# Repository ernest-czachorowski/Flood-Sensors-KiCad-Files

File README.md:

# Flood-Sensors-KiCad-Files

This repository contains KiCad files for my master's thesis IoT infrastructure, which includes water leak detection sensors. It does not include any source code as it is the intellectual property of the Nicolaus Copernicus University in Torun and cannot be published here. The infrastructure is divided into a web service made with Node.js and EJS, a PCB master board that communicates with the web service using TCP or UDP protocols, and a set of leak detection sensors that communicate with the master using the Modbus protocol and notify it when a leak is detected. The Master board sends a notification message to the web service about the leak.

### Folder Structure:

- Master - KiCad project of the Master PCB
- Slave - KiCad project of the Slave PCB
- Datasheet - datasheets of used chips/components
- KiCad_symbols - KiCad library files made by me
- Pictures - some pictures

### Master Board:

The Master board is responsible for managing communication between the web service and the Slave boards. It features an ATmega128 microcontroller, which has more RAM memory than the ATmega32 mentioned in the documentation. Communication with the web service is handled by the ENC28J60 chip, and to communicate with slaves, the MAX485 chip is used.

### Slave Board:

The Slave board detects water leaks and communicates with the Master board using the MAX485 chip. It features an LM393 chip for detecting the leak and is controlled by an ATmega32 microcontroller.

### Web Service:

The web service is built using Node.js and EJS and is responsible for receiving notification messages from the Master board about water leaks. It allows users to view the status of the system.

### License:

This project is licensed under the MIT License - see the LICENSE file for details.

### Working devices:

### Master board:

### Slave board:

### Prototype board:

### Prototype board:

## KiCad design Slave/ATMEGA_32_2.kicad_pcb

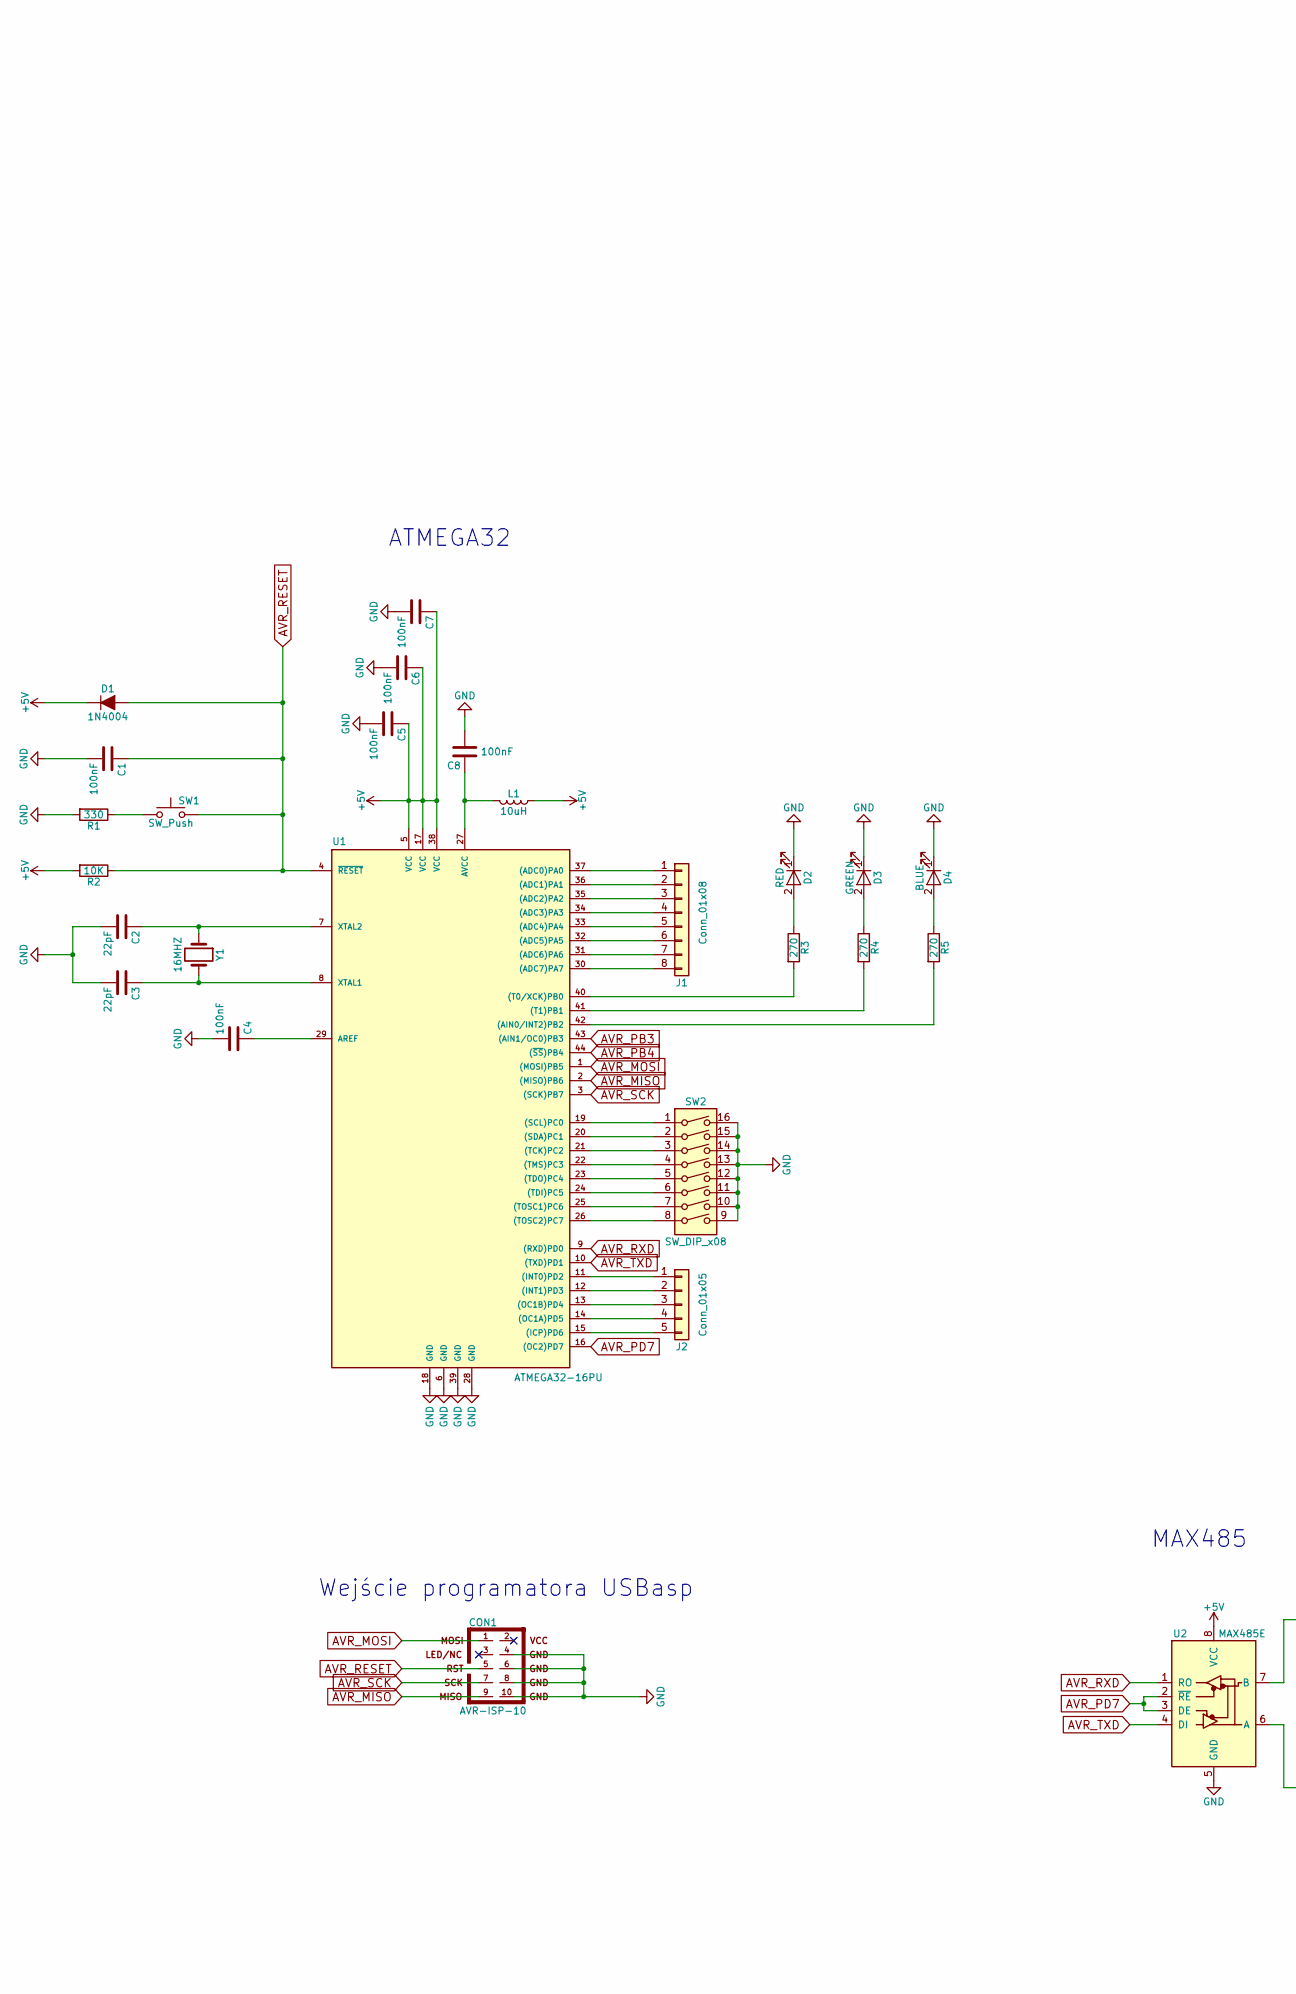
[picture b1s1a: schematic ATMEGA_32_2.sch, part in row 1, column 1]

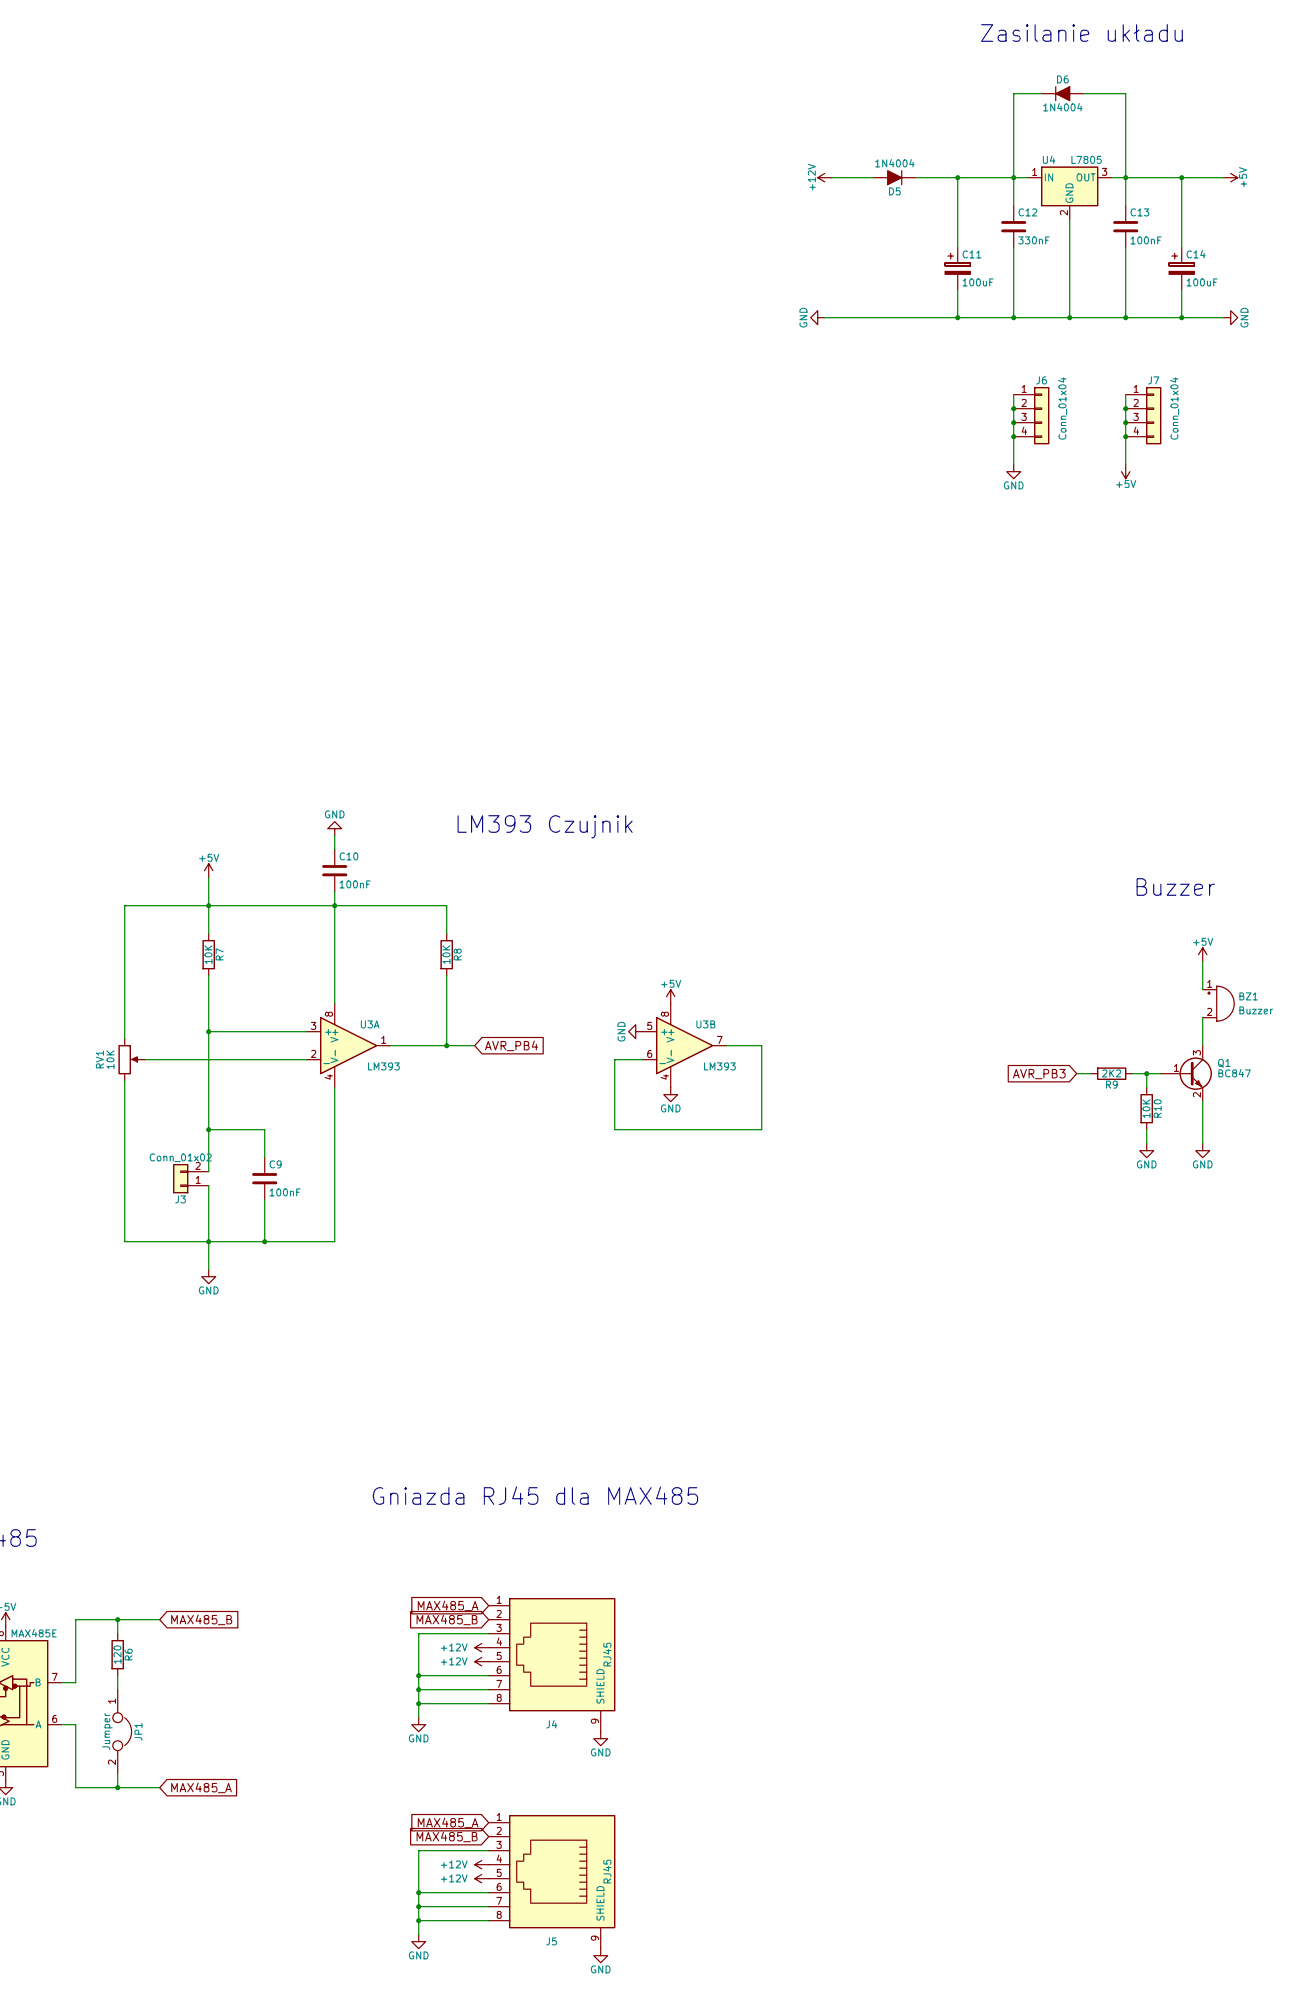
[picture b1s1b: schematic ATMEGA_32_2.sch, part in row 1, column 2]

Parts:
BZ1: Buzzer; Buzzer_12x9.5RM7.6
C1, C4, C5, C6, C7, C8, C9, C10, C13: 100nF; C_1206_HandSoldering
C2, C3: 22pF; C_1206_HandSoldering
C11, C14: 100uF; CP_Elec_6.3x5.3
C12: 330nF; C_1206_HandSoldering
CON1: AVR-ISP-10; Pin_Header_Straight_2x05_Pitch2.54mm
D1, D5, D6: 1N4004; D_DO-35_SOD27_P7.62mm_Horizontal
D2: RED; LED_1206_HandSoldering
D3: GREEN; LED_1206_HandSoldering
D4: BLUE; LED_1206_HandSoldering
J1: Conn_01x08; Pin_Header_Straight_1x08_Pitch2.54mm
J2: Conn_01x05; Pin_Header_Straight_1x05_Pitch2.54mm
J3: Conn_01x02; Pin_Header_Straight_1x02_Pitch2.54mm
J4, J5: RJ45; RJ45_8
J6, J7: Conn_01x04; Pin_Header_Straight_1x04_Pitch2.54mm
JP1: Jumper; Pin_Header_Straight_1x02_Pitch2.54mm
L1: 10uH; L_1206_HandSoldering
Q1: BC847; SOT-23
R1: 330; R_1206_HandSoldering
R2, R7, R8, R10: 10K; R_1206_HandSoldering
R3, R4, R5: 270; R_1206_HandSoldering
R6: 120; R_1206_HandSoldering
R9: 2K2; R_1206_HandSoldering
RV1: 10K; Potentiometer_Trimmer_ACP_CA6v_Horizontal
SW1: SW_Push; SW_PUSH_6mm_h13mm
SW2: SW_DIP_x08; SW_DIP_x8_W7.62mm_Slide
U1: ATMEGA32-16PU; TQFP-44_10x10mm_Pitch0.8mm
U2: MAX485E; SOIC-8_3.9x4.9mm_Pitch1.27mm
U3: LM393; SOIC-8_3.9x4.9mm_Pitch1.27mm
U4: L7805; TO-220-3_Vertical
Y1: 16MHZ; Crystal_HC49-U_Vertical

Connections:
+5V: BZ1.1 (-), C5.1, C6.1, C7.1, C10.2, C13.1, C14.1, D1.1 (K), D6.2 (A), J7.1, J7.2, J7.3, J7.4, L1.1, R2.2, R7.1, R8.1, RV1.1, U1.5 (VCC), U1.17 (VCC), U1.38 (VCC), U2.8 (VCC), U3.8 (V+), U4.3 (OUT)
+12V: D5.2 (A), J4.4, J4.5, J5.4, J5.5
AVR_MISO: CON1.9, U1.2 ((MISO)PB6)
AVR_MOSI: CON1.1, U1.1 ((MOSI)PB5)
AVR_PB3: R9.2, U1.43 ((AIN1/OC0)PB3)
AVR_PB4: R8.2, U1.44 ((~SS~)PB4), U3.1
AVR_PD7: U1.16 ((OC2)PD7), U2.2 (~RE), U2.3 (DE)
AVR_RESET: C1.1, CON1.5, D1.2 (A), R2.1, SW1.2, U1.4 (~RESET)
AVR_RXD: U1.9 ((RXD)PD0), U2.1 (RO)
AVR_SCK: CON1.7, U1.3 ((SCK)PB7)
AVR_TXD: U1.10 ((TXD)PD1), U2.4 (DI)
GND: C1.2, C2.2, C3.2, C4.2, C5.2, C6.2, C7.2, C8.2, C9.2, C10.1, C11.2, C12.2, C13.2, C14.2, CON1.4, CON1.6, CON1.8, CON1.10, D2.1 (K), D3.1 (K), D4.1 (K), J3.1, J4.3, J4.6, J4.7, J4.8, J4.9 (SHIELD), J5.3, J5.6, J5.7, J5.8, J5.9 (SHIELD), J6.1, J6.2, J6.3, J6.4, Q1.2 (E), R1.2, R10.2, RV1.3, SW2.9, SW2.10, SW2.11, SW2.12, SW2.13, SW2.14, SW2.15, SW2.16, U1.6 (GND), U1.18 (GND), U1.28 (GND), U1.39 (GND), U2.5 (GND), U3.4 (V-), U3.5 (+), U4.2 (GND)
MAX485_A: J4.1, J5.1, JP1.2, U2.6 (A)
MAX485_B: J4.2, J5.2, R6.1, U2.7 (B)
unnamed: BZ1.2 (+), Q1.3 (C)
unnamed: C2.1, U1.7 (XTAL2), Y1.1
unnamed: C3.1, U1.8 (XTAL1), Y1.2
unnamed: C4.1, U1.29 (AREF)
unnamed: C8.1, L1.2, U1.27 (AVCC)
unnamed: C9.1, J3.2, R7.2, U3.3 (+)
unnamed: C11.1, C12.1, D5.1 (K), D6.1 (K), U4.1 (IN)
unnamed: D2.2 (A), R3.1
unnamed: D3.2 (A), R4.1
unnamed: D4.2 (A), R5.1
unnamed: J1.1, U1.37 ((ADC0)PA0)
unnamed: J1.2, U1.36 ((ADC1)PA1)
unnamed: J1.3, U1.35 ((ADC2)PA2)
unnamed: J1.4, U1.34 ((ADC3)PA3)
unnamed: J1.5, U1.33 ((ADC4)PA4)
unnamed: J1.6, U1.32 ((ADC5)PA5)
unnamed: J1.7, U1.31 ((ADC6)PA6)
unnamed: J1.8, U1.30 ((ADC7)PA7)
unnamed: J2.1, U1.11 ((INT0)PD2)
unnamed: J2.2, U1.12 ((INT1)PD3)
unnamed: J2.3, U1.13 ((OC1B)PD4)
unnamed: J2.4, U1.14 ((OC1A)PD5)
unnamed: J2.5, U1.15 ((ICP)PD6)
unnamed: JP1.1, R6.2
unnamed: Q1.1 (B), R9.1, R10.1
unnamed: R1.1, SW1.1
unnamed: R3.2, U1.40 ((T0/XCK)PB0)
unnamed: R4.2, U1.41 ((T1)PB1)
unnamed: R5.2, U1.42 ((AIN0/INT2)PB2)
unnamed: RV1.2, U3.2 (_)
unnamed: SW2.1, U1.19 ((SCL)PC0)
unnamed: SW2.2, U1.20 ((SDA)PC1)
unnamed: SW2.3, U1.21 ((TCK)PC2)
unnamed: SW2.4, U1.22 ((TMS)PC3)
unnamed: SW2.5, U1.23 ((TDO)PC4)
unnamed: SW2.6, U1.24 ((TDI)PC5)
unnamed: SW2.7, U1.25 ((TOSC1)PC6)
unnamed: SW2.8, U1.26 ((TOSC2)PC7)
unnamed: U3.6 (_), U3.7

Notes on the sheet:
Wejście programatora USBasp
ATMEGA32
Zasilanie układu
MAX485
Gniazda RJ45 dla MAX485
LM393 Czujnik
Buzzer

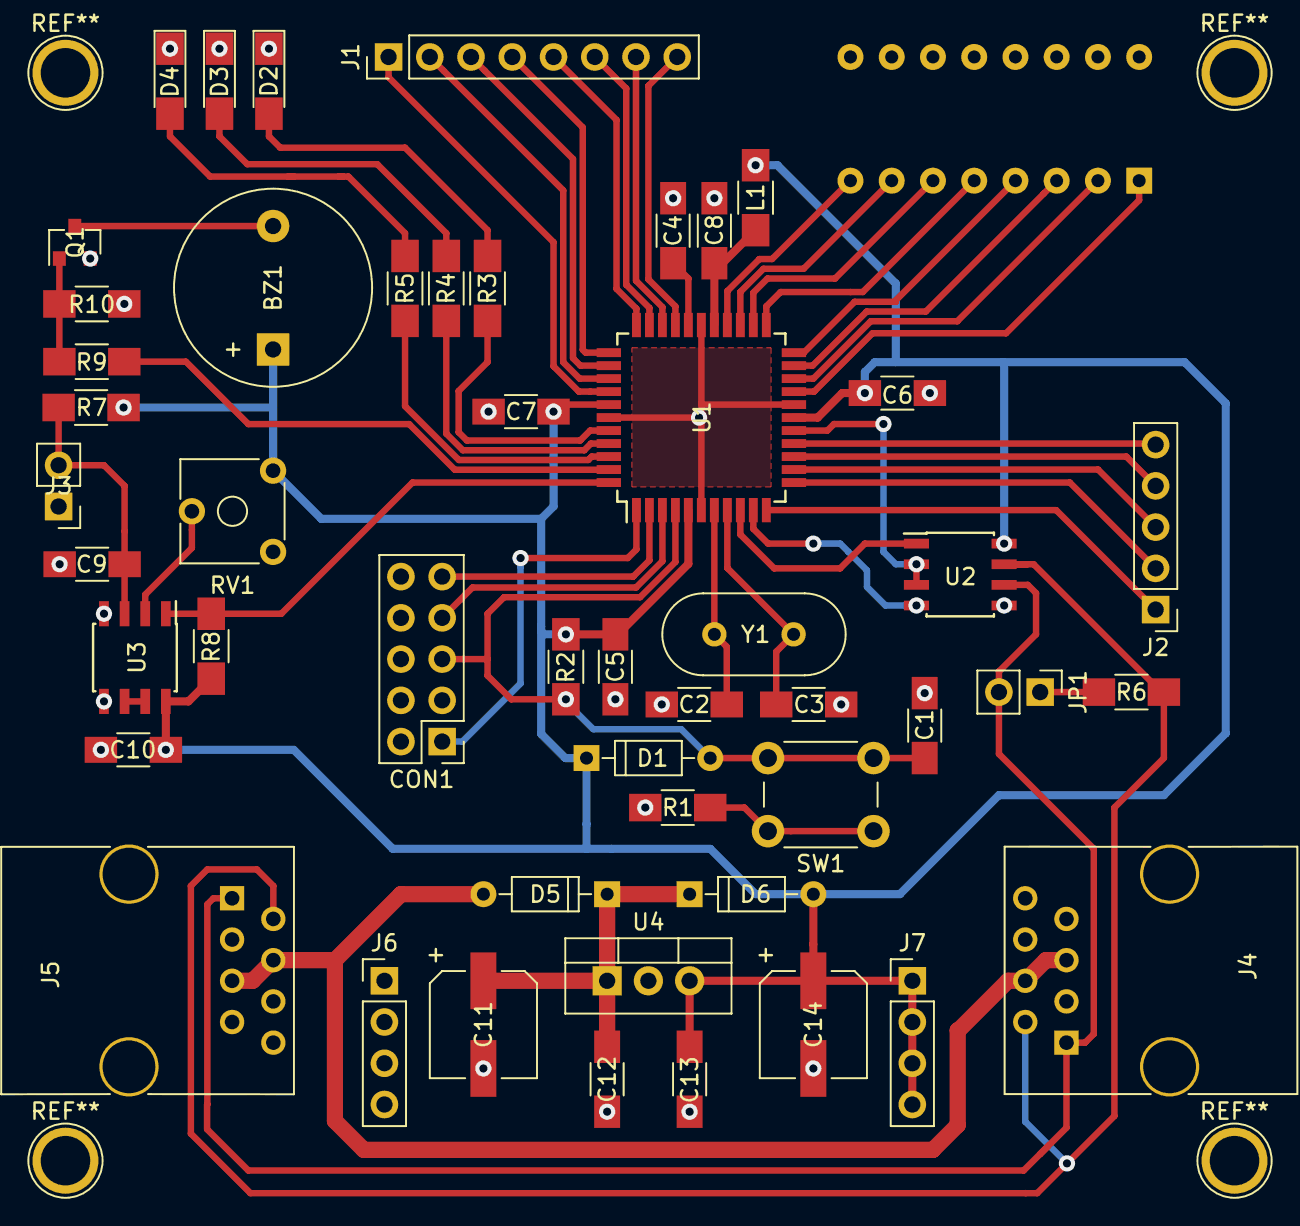
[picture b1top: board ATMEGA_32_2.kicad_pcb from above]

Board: 2 copper layers, 50 parts (1 on the bottom side), 53 nets.
